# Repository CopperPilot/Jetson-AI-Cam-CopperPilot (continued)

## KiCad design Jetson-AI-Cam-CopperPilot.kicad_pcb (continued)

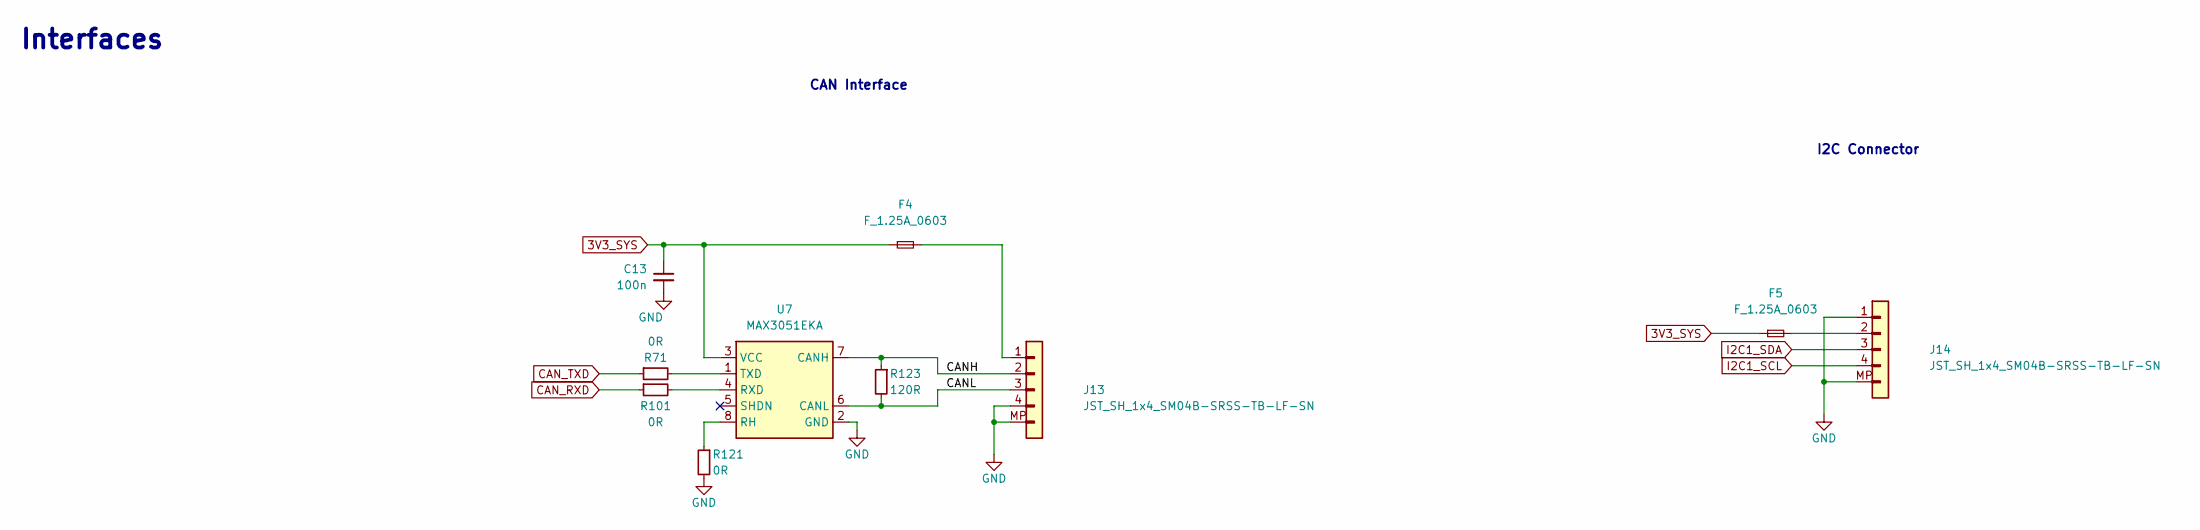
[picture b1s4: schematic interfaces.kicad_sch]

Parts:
C13: C_100n_0402; C_0402_1005Metric; Voltage 50V; MPN GRM155R61H104KE14D; LCSC C1525
F4, F5: F_1.25A_0603; F_0603_1608Metric; MPN 04671.25NR; LCSC C150891
J13, J14: JST_SH_1x4_SM04B-SRSS-TB-LF-SN; Conn_JST_SH_1x4_SM04B-SRSS-TB-LF-SN; MPN SM04B-SRSS-TB(LF)(SN); LCSC C160404
R71, R101, R121: R_0R_0402; R_0402_1005Metric; MPN ERJ2GE0R00X; LCSC C17168
R123: R_120R_0402; R_0402_1005Metric; Tolerance 1%; MPN CR0402-FX-1200GLF; LCSC C25079
U7: MAX3051EKA; SOT-23-8; MPN MAX3051EKA; LCSC C90741

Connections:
3V3_SYS: C13.1, F4.1, F5.1, U7.3 (VCC); also elsewhere on the board
/Interfaces/CANH: J13.2, R123.1, U7.7 (CANH)
/Interfaces/CANL: J13.3, R123.2, U7.6 (CANL)
CAN_RXD: R101.1; also elsewhere on the board
CAN_TXD: R71.1; also elsewhere on the board
GND: C13.2, J13.4, J13.MP, J14.1, J14.MP, R121.2, U7.2 (GND); also elsewhere on the board
I2C1_SCL: J14.4; also elsewhere on the board
I2C1_SDA: J14.3; also elsewhere on the board
unnamed: F4.2, J13.1
unnamed: F5.2, J14.2
unnamed: R121.1, U7.8 (RH)
unnamed: R101.2, U7.4 (RXD)
unnamed: R71.2, U7.1 (TXD)

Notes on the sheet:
I2C Connector
CAN Interface
Interfaces

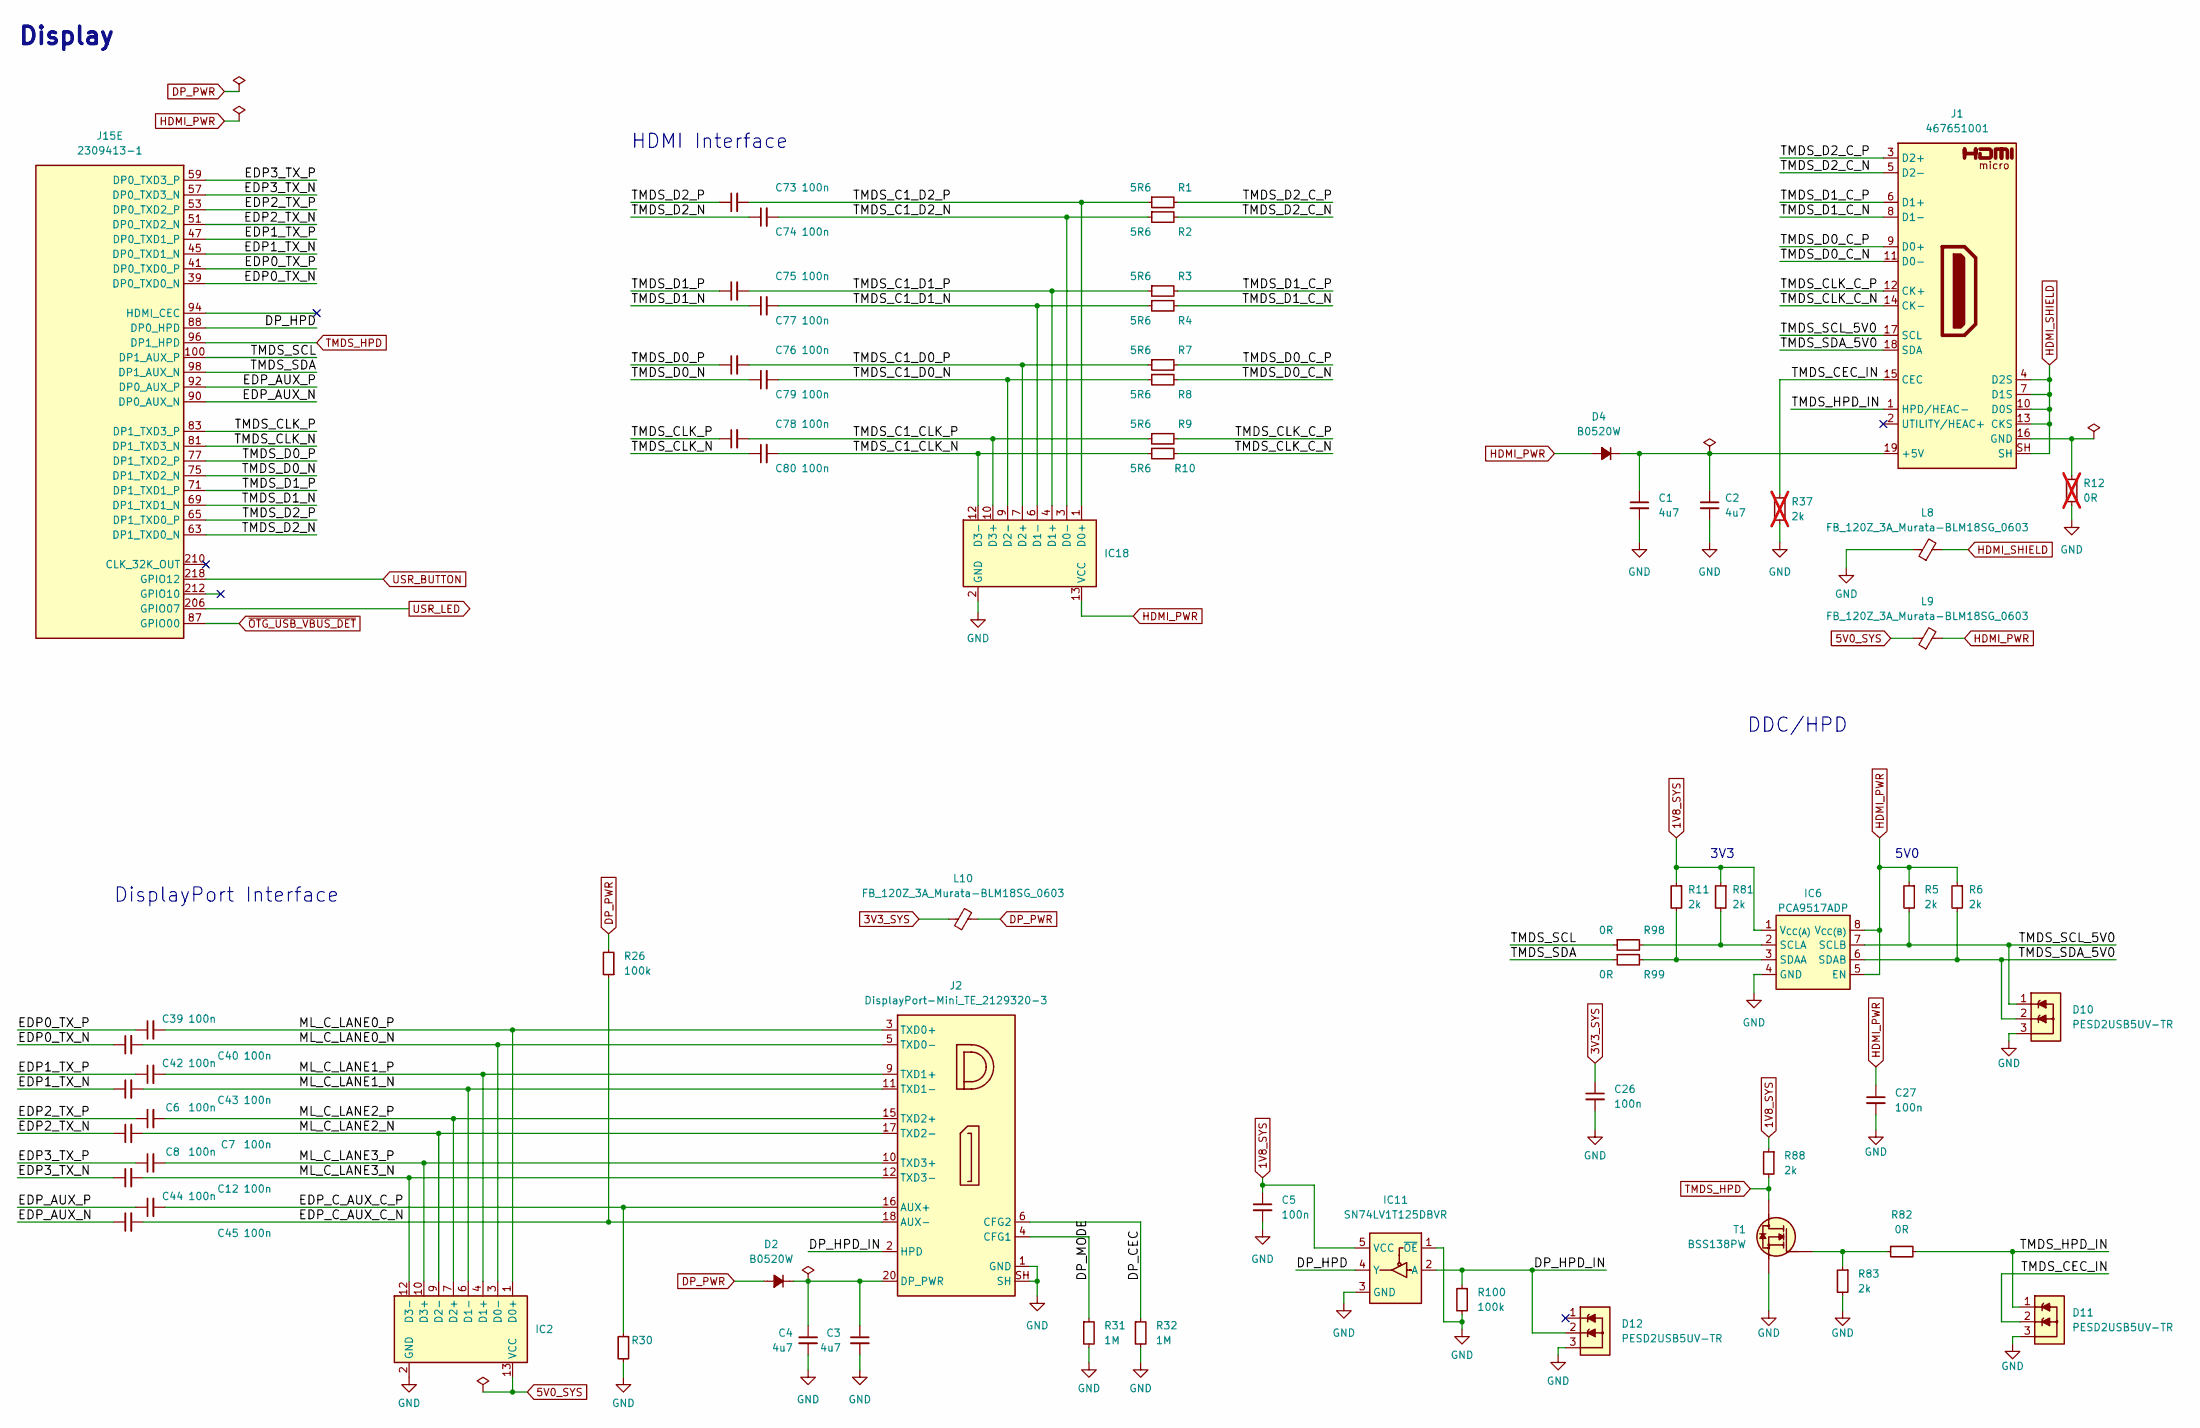
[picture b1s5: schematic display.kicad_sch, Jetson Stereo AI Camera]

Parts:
C1, C2, C3, C4: C_4u7_0402; C_0402_1005Metric; MPN GRM155R61A475MEAAD; LCSC C23733
C5, C6, C7, C8, C12, C26, C27, C39, C40, C42, C43, C44, C45, C73, C74, C75, C76, C77, C78, C79, C80: C_100n_0402; C_0402_1005Metric; Voltage 50V; MPN GRM155R61H104KE14D; LCSC C1525
D2, D4: B0520W; D_SOD-323F; MPN B0520W; LCSC C8598
D10, D11, D12: PESD2USB5UV-TR; SOT-23-3; MPN PESD2USB5UV-TR; LCSC C2827695
IC2, IC18: TPD8S009DSMR; R-PDSO-N15; PartSymbol TPD8S009DSMR; LCSC C139543
IC6: PCA9517ADP; TSSOP-8_3x3mm_P0.65mm; MPN PCA9517ADP; LCSC C112457
IC11: SN74LV1T125DBVR; SOT-23-5; MPN SN74LV1T125DBVR; LCSC C100024
J1: HDMI-Micro-D_Molex_467561001; HDMI-Micro-D_Receptacle_Molex_467651001; MPN 467651001; LCSC C563878
J2: DisplayPort-Mini_TE_2129320-3; DisplayPort-Mini_Receptacle_TE_2129320-3; MPN 2129320-3; LCSC C574827
J15: Bus_DDR4_SODIMM_CUSTOM_Jetson-Nano-H9.2mm-socket; TE_2309413; PartSymbol 2309413-1; LCSC C2766246
L8, L9, L10: FB_120Z_3A_Murata-BLM18SG_0603; FB_0603_1608Metric; MPN BLM18SG121TN1D; LCSC C73884
R1, R2, R3, R4, R7, R8, R9, R10: R_5R6_0402; R_0402_1005Metric; Tolerance 1%; MPN CR0402-FX-5R60GLF; LCSC C25122
R5, R6, R11, R81, R83, R88: R_2k_0402; R_0402_1005Metric; Tolerance 1%; MPN CR0402-FX-2001GLF; LCSC C4109
R12: R_0R_0402; R_0402_1005Metric; MPN ERJ2GE0R00X; LCSC C17168; not fitted
R26, R30, R100: R_100k_0402; R_0402_1005Metric; Tolerance 1%; MPN CR0402-FX-1003GLF; LCSC C25741
R31, R32: R_1M_0402; R_0402_1005Metric; Tolerance 1%; MPN CR0402-FX-1004GLF; LCSC C26083
R37: R_2k_0402; R_0402_1005Metric; Tolerance 1%; MPN CR0402-FX-2001GLF; LCSC C4109; not fitted
R82, R98, R99: R_0R_0402; R_0402_1005Metric; MPN ERJ2GE0R00X; LCSC C17168
T1: BSS138PW; SC70-3; MPN BSS138PW; LCSC C84617

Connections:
1V8_SYS: C5.1, IC6.1 (V_{CC(A)}), IC11.5 (VCC), R11.1, R81.1, R88.1; also elsewhere on the board
3V3_SYS: C26.1, L10.1; also elsewhere on the board
5V0_SYS: IC2.13 (VCC), IC2.15 (VCC), L9.1; also elsewhere on the board
/Display/DP_CEC: J2.6 (CFG2), R32.1
/Display/DP_HPD: IC11.4 (Y), J15.88 (DP0_HPD)
/Display/DP_HPD_IN: D12.2, IC11.2 (A), J2.2 (HPD), R100.1
/Display/DP_MODE: J2.4 (CFG1), R31.1
/Display/EDP0_TX_N: C40.1, J15.39 (DP0_TXD0_N)
/Display/EDP0_TX_P: C39.1, J15.41 (DP0_TXD0_P)
/Display/EDP1_TX_N: C43.1, J15.45 (DP0_TXD1_N)
/Display/EDP1_TX_P: C42.1, J15.47 (DP0_TXD1_P)
/Display/EDP2_TX_N: C7.1, J15.51 (DP0_TXD2_N)
/Display/EDP2_TX_P: C6.1, J15.53 (DP0_TXD2_P)
/Display/EDP3_TX_N: C12.1, J15.57 (DP0_TXD3_N)
/Display/EDP3_TX_P: C8.1, J15.59 (DP0_TXD3_P)
/Display/EDP_AUX_N: C45.1, J15.90 (DP0_AUX_N)
/Display/EDP_AUX_P: C44.1, J15.92 (DP0_AUX_P)
/Display/EDP_C_AUX_C_N: C45.2, J2.18 (AUX-), R26.1
/Display/EDP_C_AUX_C_P: C44.2, J2.16 (AUX+), R30.1
/Display/ML_C_LANE0_N: C40.2, IC2.3 (D0-), J2.5 (TXD0-)
/Display/ML_C_LANE0_P: C39.2, IC2.1 (D0+), J2.3 (TXD0+)
/Display/ML_C_LANE1_N: C43.2, IC2.6 (D1-), J2.11 (TXD1-)
/Display/ML_C_LANE1_P: C42.2, IC2.4 (D1+), J2.9 (TXD1+)
/Display/ML_C_LANE2_N: C7.2, IC2.9 (D2-), J2.17 (TXD2-)
/Display/ML_C_LANE2_P: C6.2, IC2.7 (D2+), J2.15 (TXD2+)
/Display/ML_C_LANE3_N: C12.2, IC2.12 (D3-), J2.12 (TXD3-)
/Display/ML_C_LANE3_P: C8.2, IC2.10 (D3+), J2.10 (TXD3+)
/Display/TMDS_C1_CLK_N: C80.2, IC18.12 (D3-), R10.1
/Display/TMDS_C1_CLK_P: C78.2, IC18.10 (D3+), R9.1
/Display/TMDS_C1_D0_N: C79.2, IC18.9 (D2-), R8.1
/Display/TMDS_C1_D0_P: C76.2, IC18.7 (D2+), R7.1
/Display/TMDS_C1_D1_N: C77.2, IC18.6 (D1-), R4.1
/Display/TMDS_C1_D1_P: C75.2, IC18.4 (D1+), R3.1
/Display/TMDS_C1_D2_N: C74.2, IC18.3 (D0-), R2.1
/Display/TMDS_C1_D2_P: C73.2, IC18.1 (D0+), R1.1
/Display/TMDS_CEC_IN: D11.2, J1.15 (CEC), R37.1
/Display/TMDS_CLK_C_N: J1.14 (CK-), R10.2
/Display/TMDS_CLK_C_P: J1.12 (CK+), R9.2
/Display/TMDS_CLK_N: C80.1, J15.81 (DP1_TXD3_N)
/Display/TMDS_CLK_P: C78.1, J15.83 (DP1_TXD3_P)
/Display/TMDS_D0_C_N: J1.11 (D0-), R8.2
/Display/TMDS_D0_C_P: J1.9 (D0+), R7.2
/Display/TMDS_D0_N: C79.1, J15.75 (DP1_TXD2_N)
/Display/TMDS_D0_P: C76.1, J15.77 (DP1_TXD2_P)
/Display/TMDS_D1_C_N: J1.8 (D1-), R4.2
/Display/TMDS_D1_C_P: J1.6 (D1+), R3.2
/Display/TMDS_D1_N: C77.1, J15.69 (DP1_TXD1_N)
/Display/TMDS_D1_P: C75.1, J15.71 (DP1_TXD1_P)
/Display/TMDS_D2_C_N: J1.5 (D2-), R2.2
/Display/TMDS_D2_C_P: J1.3 (D2+), R1.2
/Display/TMDS_D2_N: C74.1, J15.63 (DP1_TXD0_N)
/Display/TMDS_D2_P: C73.1, J15.65 (DP1_TXD0_P)
/Display/TMDS_HPD_IN: D11.1, J1.1 (HPD/HEAC-), R82.2
/Display/TMDS_SCL: J15.100 (DP1_AUX_P), R98.1
/Display/TMDS_SCL_5V0: D10.1, IC6.7 (SCLB), J1.17 (SCL), R5.2
/Display/TMDS_SDA: J15.98 (DP1_AUX_N), R99.1
/Display/TMDS_SDA_5V0: D10.2, IC6.6 (SDAB), J1.18 (SDA), R6.2
DP_PWR: D2.2 (A), L10.2, R26.2
GND: C1.2, C2.2, C3.2, C4.2, C5.2, C26.2, C27.2, D10.3, D11.3, D12.3, IC2.2 (GND), IC2.5 (GND), IC2.8 (GND), IC2.11 (GND), IC6.4 (GND), IC11.1 (~OE), IC11.3 (GND), IC18.2 (GND), IC18.5 (GND), IC18.8 (GND), IC18.11 (GND), J2.1 (GND), J2.7 (GND), J2.8 (GND), J2.13 (GND), J2.14 (GND), J2.19 (GND), J2.SH, L8.1, R12.2, R30.2, R31.2, R32.2, R37.2, R83.2, R100.2, T1.2 (S); also elsewhere on the board
HDMI_PWR: C27.1, D4.2 (A), IC6.5 (EN), IC6.8 (V_{CC(B)}), IC18.13 (VCC), IC18.15 (VCC), L9.2, R5.1, R6.1
HDMI_SHIELD: J1.4 (D2S), J1.7 (D1S), J1.10 (D0S), J1.13 (CKS), J1.SH, L8.2
unnamed: C3.1, C4.1, D2.1 (C), J2.20 (DP_PWR)
unnamed: C1.1, C2.1, D4.1 (C), J1.19 (+5V)
unnamed: IC6.2 (SCLA), R81.2, R98.2
unnamed: IC6.3 (SDAA), R11.2, R99.2
unnamed: J1.16 (GND), R12.1
unnamed: R82.1, R83.1, T1.1 (G)
TMDS_HPD: J15.96 (DP1_HPD), R88.2, T1.3 (D)
USR_BUTTON: J15.218 (GPIO12); also elsewhere on the board
USR_LED: J15.206 (GPIO07); also elsewhere on the board
~OTG_USB_VBUS_DET: J15.87 (GPIO00); also elsewhere on the board

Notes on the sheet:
5V0
DDC/HPD
3V3
HDMI Interface
DisplayPort Interface
Display

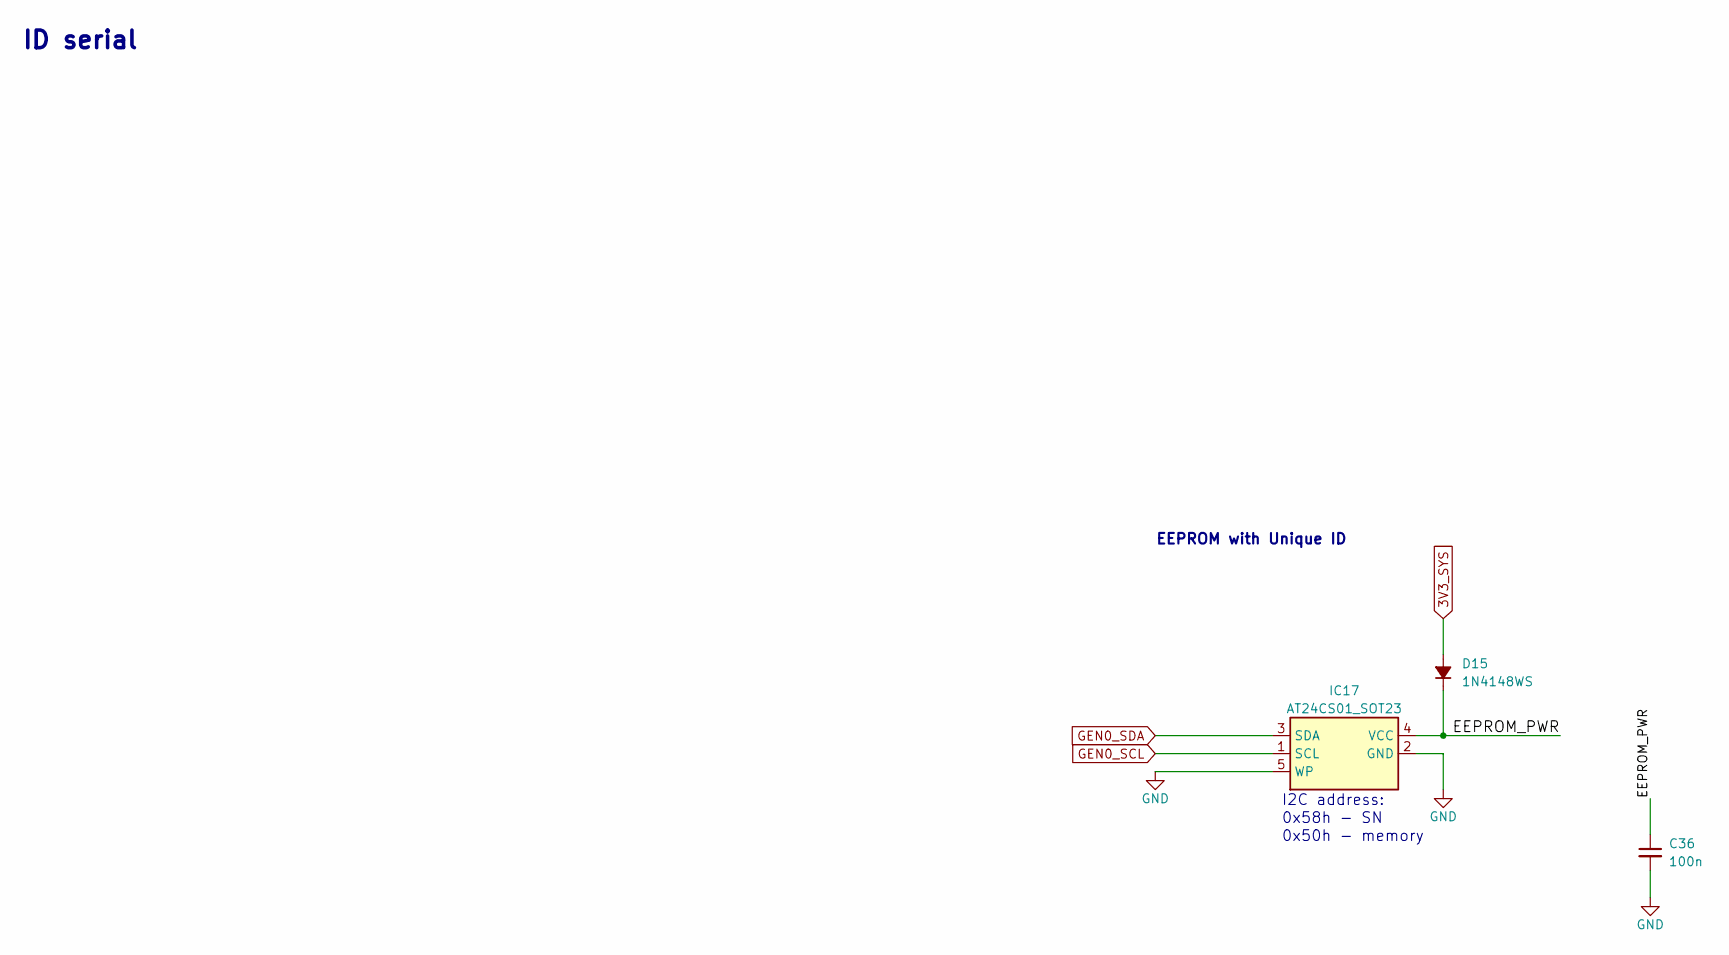
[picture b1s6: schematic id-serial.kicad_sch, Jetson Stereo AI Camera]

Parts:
C36: C_100n_0402; C_0402_1005Metric; Voltage 50V; MPN GRM155R61H104KE14D; LCSC C1525
D15: 1N4148WS; D_SOD-323F; MPN 1N4148WS; LCSC C2128
IC17: AT24CS01_SOT23; SOT-23-5; MPN AT24CS01-ST; LCSC C500682

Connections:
3V3_SYS: D15.2 (A); also elsewhere on the board
/ID Serial/EEPROM_PWR: C36.1, D15.1 (C), IC17.4 (VCC)
GEN0_SCL: IC17.1 (SCL); also elsewhere on the board
GEN0_SDA: IC17.3 (SDA); also elsewhere on the board
GND: C36.2, IC17.2 (GND), IC17.5 (WP); also elsewhere on the board

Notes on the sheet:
ID serial
0x50h - memory
I2C address:
0x58h - SN
EEPROM with Unique ID

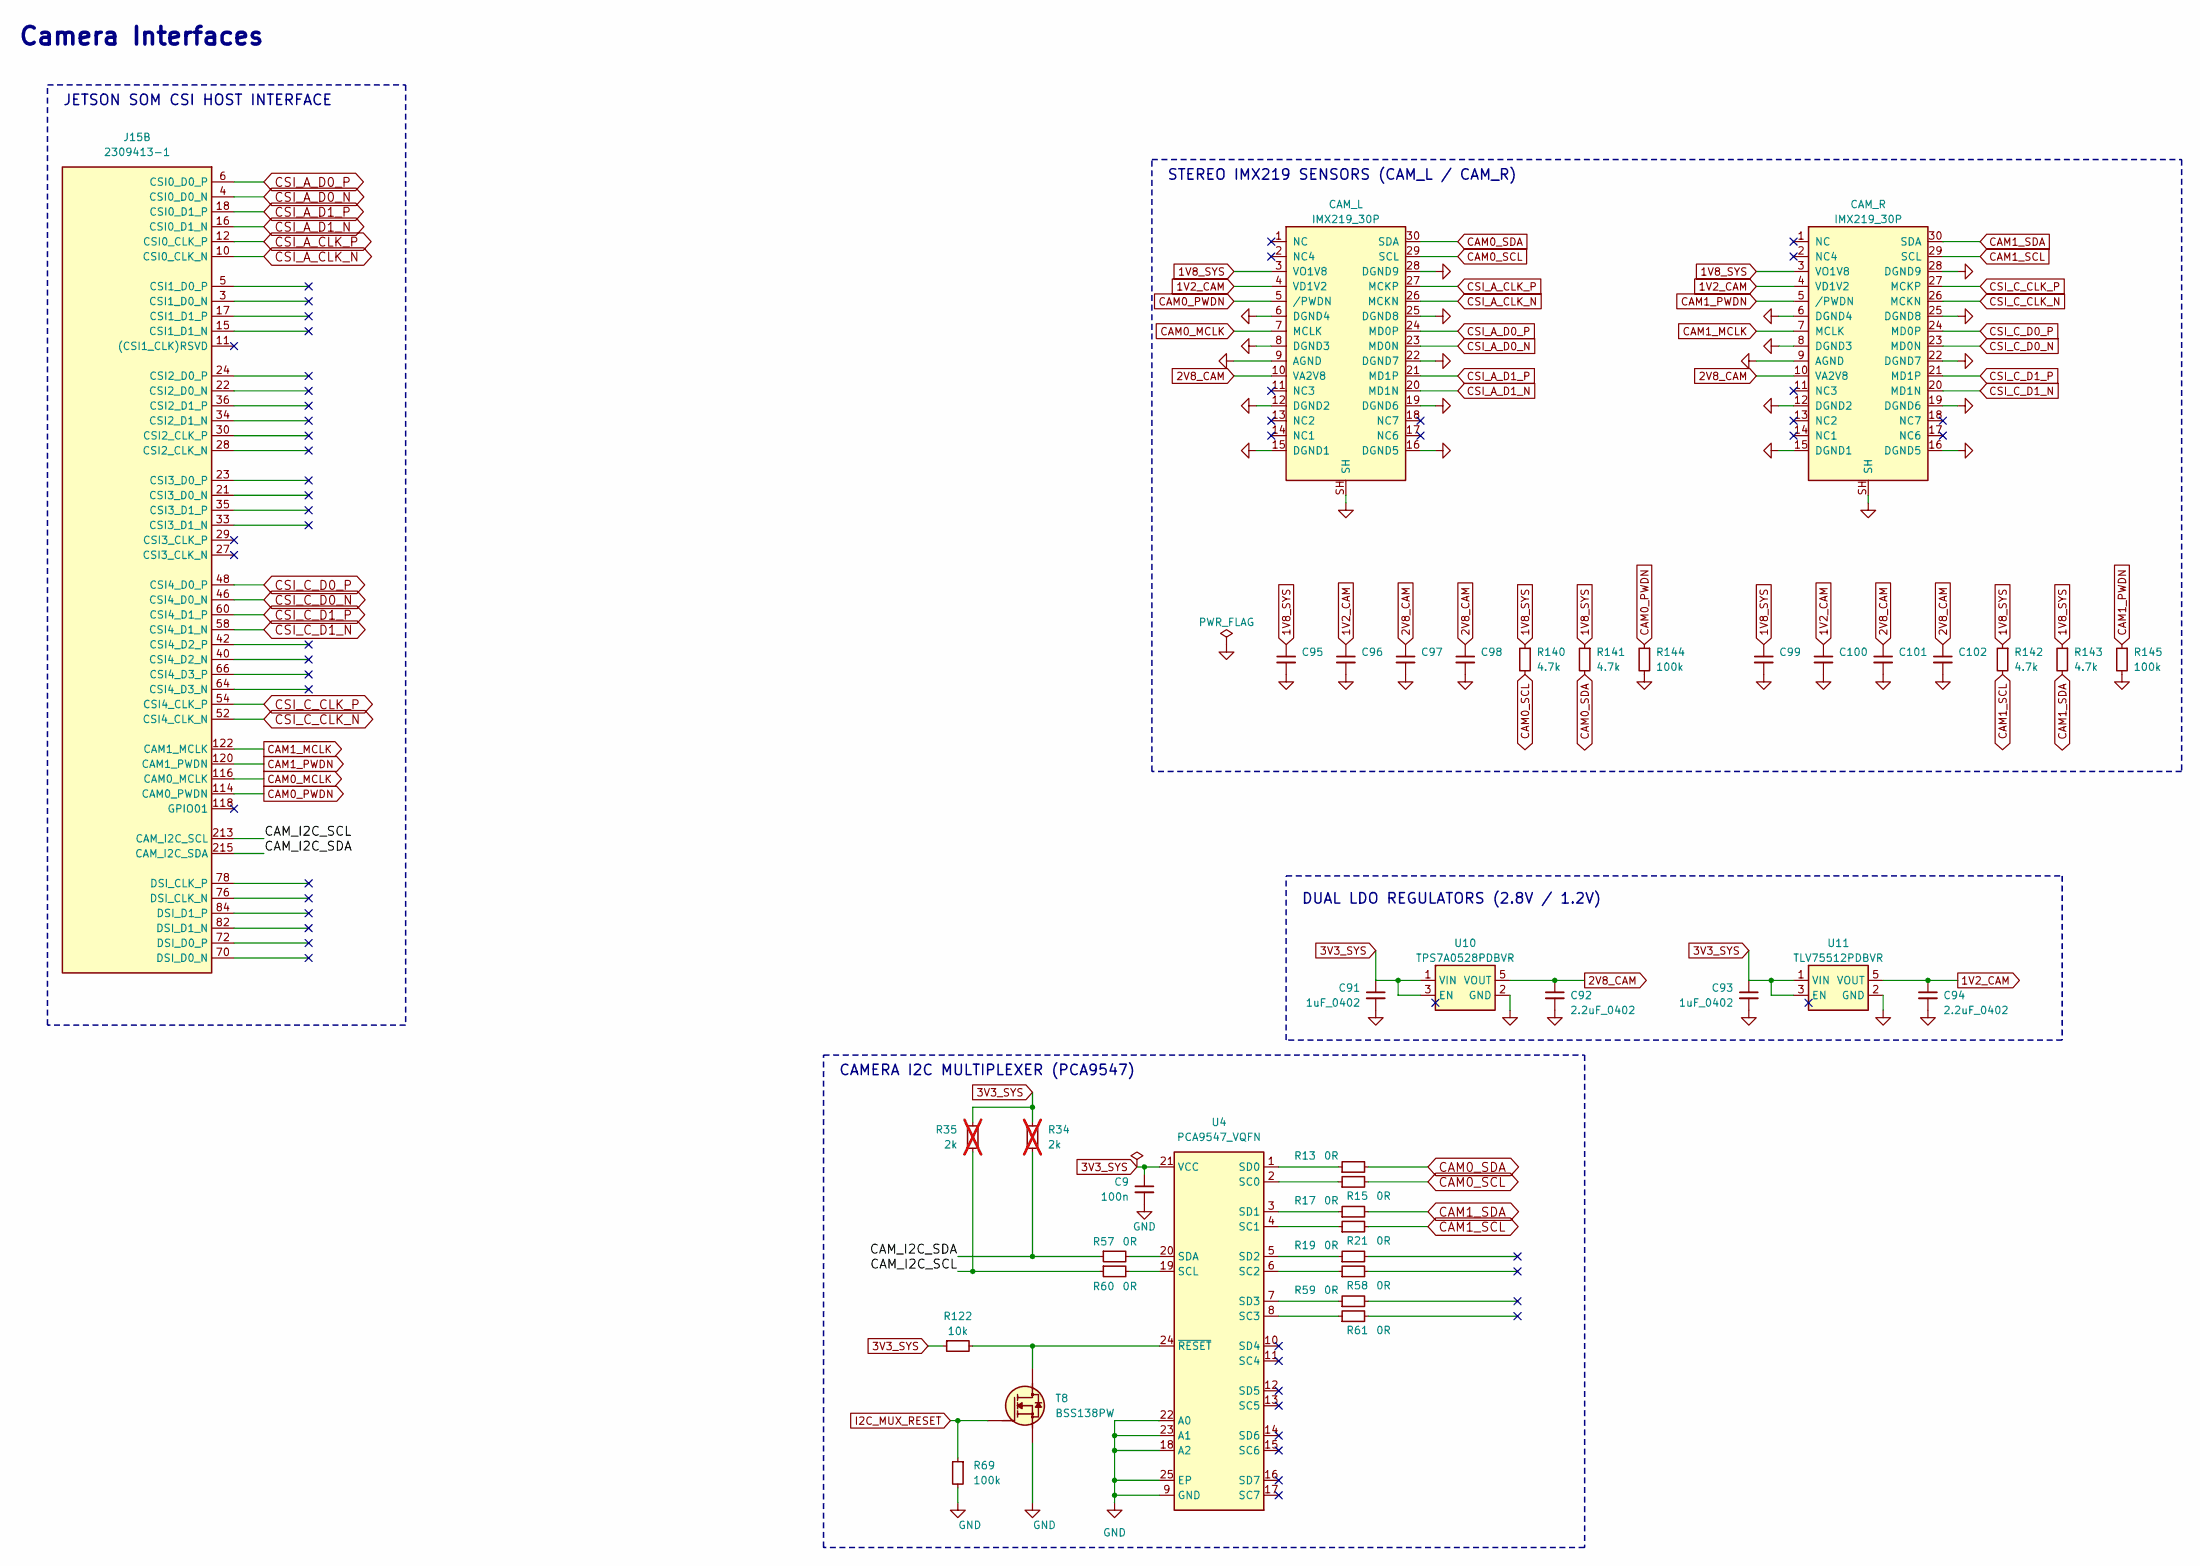
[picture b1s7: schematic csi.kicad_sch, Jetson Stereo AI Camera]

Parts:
C9: C_100n_0402; C_0402_1005Metric; Voltage 50V; MPN GRM155R61H104KE14D; LCSC C1525
C91, C93: 1uF_0402; C_0402_1005Metric; MPN C1005X6S1A105K050BC; LCSC C52923
C92, C94: 2.2uF_0402; C_0402_1005Metric; MPN C1005X5R1A225K050BC; LCSC C12530
C95, C96, C97, C99, C100, C101: C_100n_0402; C_0402_1005Metric; MPN GRM155R61H104KE14D; LCSC C1525
C98, C102: C_2u2_0402; C_0402_1005Metric; MPN C1005X5R1A225K050BC; LCSC C12530
CAM_L: IMX219_30P; Camera_Module_IMX219-D160; MPN BM20B(0.8)-30DS-0.4V(51); LCSC C424662
CAM_R: IMX219_30P; Camera_Module_IMX219-D160; MPN BM20B(0.8)-30DS-0.4V(51); LCSC C424662
J15: Bus_DDR4_SODIMM_CUSTOM_Jetson-Nano-H9.2mm-socket; TE_2309413; PartSymbol 2309413-1; LCSC C2766246
R13, R15, R17, R19, R21, R57, R58, R59, R60, R61: R_0R_0402; R_0402_1005Metric; MPN ERJ2GE0R00X; LCSC C17168
R34, R35: R_2k_0402; R_0402_1005Metric; Tolerance 1%; MPN CR0402-FX-2001GLF; LCSC C4109; not fitted
R69: R_100k_0402; R_0402_1005Metric; Tolerance 1%; MPN CR0402-FX-1003GLF; LCSC C25741
R122: R_10k_0402; R_0402_1005Metric; Tolerance 1%; MPN CR0402-FX-1002GLF; LCSC C25744
R140, R141, R142, R143: 4.7k; R_0402_1005Metric; MPN CR0402-FX-4701GLF; LCSC C25900
R144, R145: 100k; R_0402_1005Metric; MPN CR0402-FX-1003GLF; LCSC C25741
T8: BSS138PW; SC70-3; MPN BSS138PW; LCSC C84617
U4: PCA9547_VQFN; VQFN-24-1EP_3.8x3.8x1.0mm_P0.5mm; MPN PCA9547BS,118; LCSC C138804
U10: TPS7A0528PDBVR; SOT-23-5; MPN TPS7A0528PDBVR; LCSC C194387
U11: TLV75512PDBVR; SOT-23-5; MPN TLV75512PDBVR; LCSC C485675

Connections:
1V2_CAM: C94.1, C96.1, C100.1, CAM_L.4 (VD1V2), CAM_R.4 (VD1V2), U11.5 (VOUT)
1V8_SYS: C95.1, C99.1, CAM_L.3 (VO1V8), CAM_R.3 (VO1V8), R140.1, R141.1, R142.1, R143.1; also elsewhere on the board
2V8_CAM: C92.1, C97.1, C98.1, C101.1, C102.1, CAM_L.10 (VA2V8), CAM_R.10 (VA2V8), U10.5 (VOUT)
3V3_SYS: C9.1, C91.1, C93.1, R34.1, R35.1, R122.1, U4.21 (VCC), U10.1 (VIN), U10.3 (EN), U11.1 (VIN), U11.3 (EN); also elsewhere on the board
/CSI/CAM_I2C_SCL: J15.213 (CAM_I2C_SCL), R35.2, R60.1
/CSI/CAM_I2C_SDA: J15.215 (CAM_I2C_SDA), R34.2, R57.1
CAM0_MCLK: CAM_L.7 (MCLK), J15.116 (CAM0_MCLK)
CAM0_PWDN: CAM_L.5 (/PWDN), J15.114 (CAM0_PWDN), R144.1
CAM0_SCL: CAM_L.29 (SCL), R15.2, R140.2
CAM0_SDA: CAM_L.30 (SDA), R13.2, R141.2
CAM1_MCLK: CAM_R.7 (MCLK), J15.122 (CAM1_MCLK)
CAM1_PWDN: CAM_R.5 (/PWDN), J15.120 (CAM1_PWDN), R145.1
CAM1_SCL: CAM_R.29 (SCL), R21.2, R142.2
CAM1_SDA: CAM_R.30 (SDA), R17.2, R143.2
CSI_A_CLK_N: CAM_L.26 (MCKN), J15.10 (CSI0_CLK_N)
CSI_A_CLK_P: CAM_L.27 (MCKP), J15.12 (CSI0_CLK_P)
CSI_A_D0_N: CAM_L.23 (MD0N), J15.4 (CSI0_D0_N)
CSI_A_D0_P: CAM_L.24 (MD0P), J15.6 (CSI0_D0_P)
CSI_A_D1_N: CAM_L.20 (MD1N), J15.16 (CSI0_D1_N)
CSI_A_D1_P: CAM_L.21 (MD1P), J15.18 (CSI0_D1_P)
CSI_C_CLK_N: CAM_R.26 (MCKN), J15.52 (CSI4_CLK_N)
CSI_C_CLK_P: CAM_R.27 (MCKP), J15.54 (CSI4_CLK_P)
CSI_C_D0_N: CAM_R.23 (MD0N), J15.46 (CSI4_D0_N)
CSI_C_D0_P: CAM_R.24 (MD0P), J15.48 (CSI4_D0_P)
CSI_C_D1_N: CAM_R.20 (MD1N), J15.58 (CSI4_D1_N)
CSI_C_D1_P: CAM_R.21 (MD1P), J15.60 (CSI4_D1_P)
GND: C9.2, C91.2, C92.2, C93.2, C94.2, C95.2, C96.2, C97.2, C98.2, C99.2, C100.2, C101.2, C102.2, CAM_L.6 (DGND4), CAM_L.8 (DGND3), CAM_L.9 (AGND), CAM_L.12 (DGND2), CAM_L.15 (DGND1), CAM_L.16 (DGND5), CAM_L.19 (DGND6), CAM_L.22 (DGND7), CAM_L.25 (DGND8), CAM_L.28 (DGND9), CAM_L.SH, CAM_R.6 (DGND4), CAM_R.8 (DGND3), CAM_R.9 (AGND), CAM_R.12 (DGND2), CAM_R.15 (DGND1), CAM_R.16 (DGND5), CAM_R.19 (DGND6), CAM_R.22 (DGND7), CAM_R.25 (DGND8), CAM_R.28 (DGND9), CAM_R.SH, R69.2, R144.2, R145.2, T8.2 (S), U4.9 (GND), U4.18 (A2), U4.22 (A0), U4.23 (A1), U4.25 (EP), U10.2 (GND), U11.2 (GND); also elsewhere on the board
I2C_MUX_RESET: R69.1, T8.1 (G); also elsewhere on the board
unnamed: R122.2, T8.3 (D), U4.24 (~RESET)
unnamed: R15.1, U4.2 (SC0)
unnamed: R21.1, U4.4 (SC1)
unnamed: R58.1, U4.6 (SC2)
unnamed: R61.1, U4.8 (SC3)
unnamed: R60.2, U4.19 (SCL)
unnamed: R13.1, U4.1 (SD0)
unnamed: R17.1, U4.3 (SD1)
unnamed: R19.1, U4.5 (SD2)
unnamed: R59.1, U4.7 (SD3)
unnamed: R57.2, U4.20 (SDA)

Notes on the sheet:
Camera Interfaces
JETSON SOM CSI HOST INTERFACE
CAMERA I2C MULTIPLEXER (PCA9547)
DUAL LDO REGULATORS (2.8V / 1.2V)
STEREO IMX219 SENSORS (CAM_L / CAM_R)

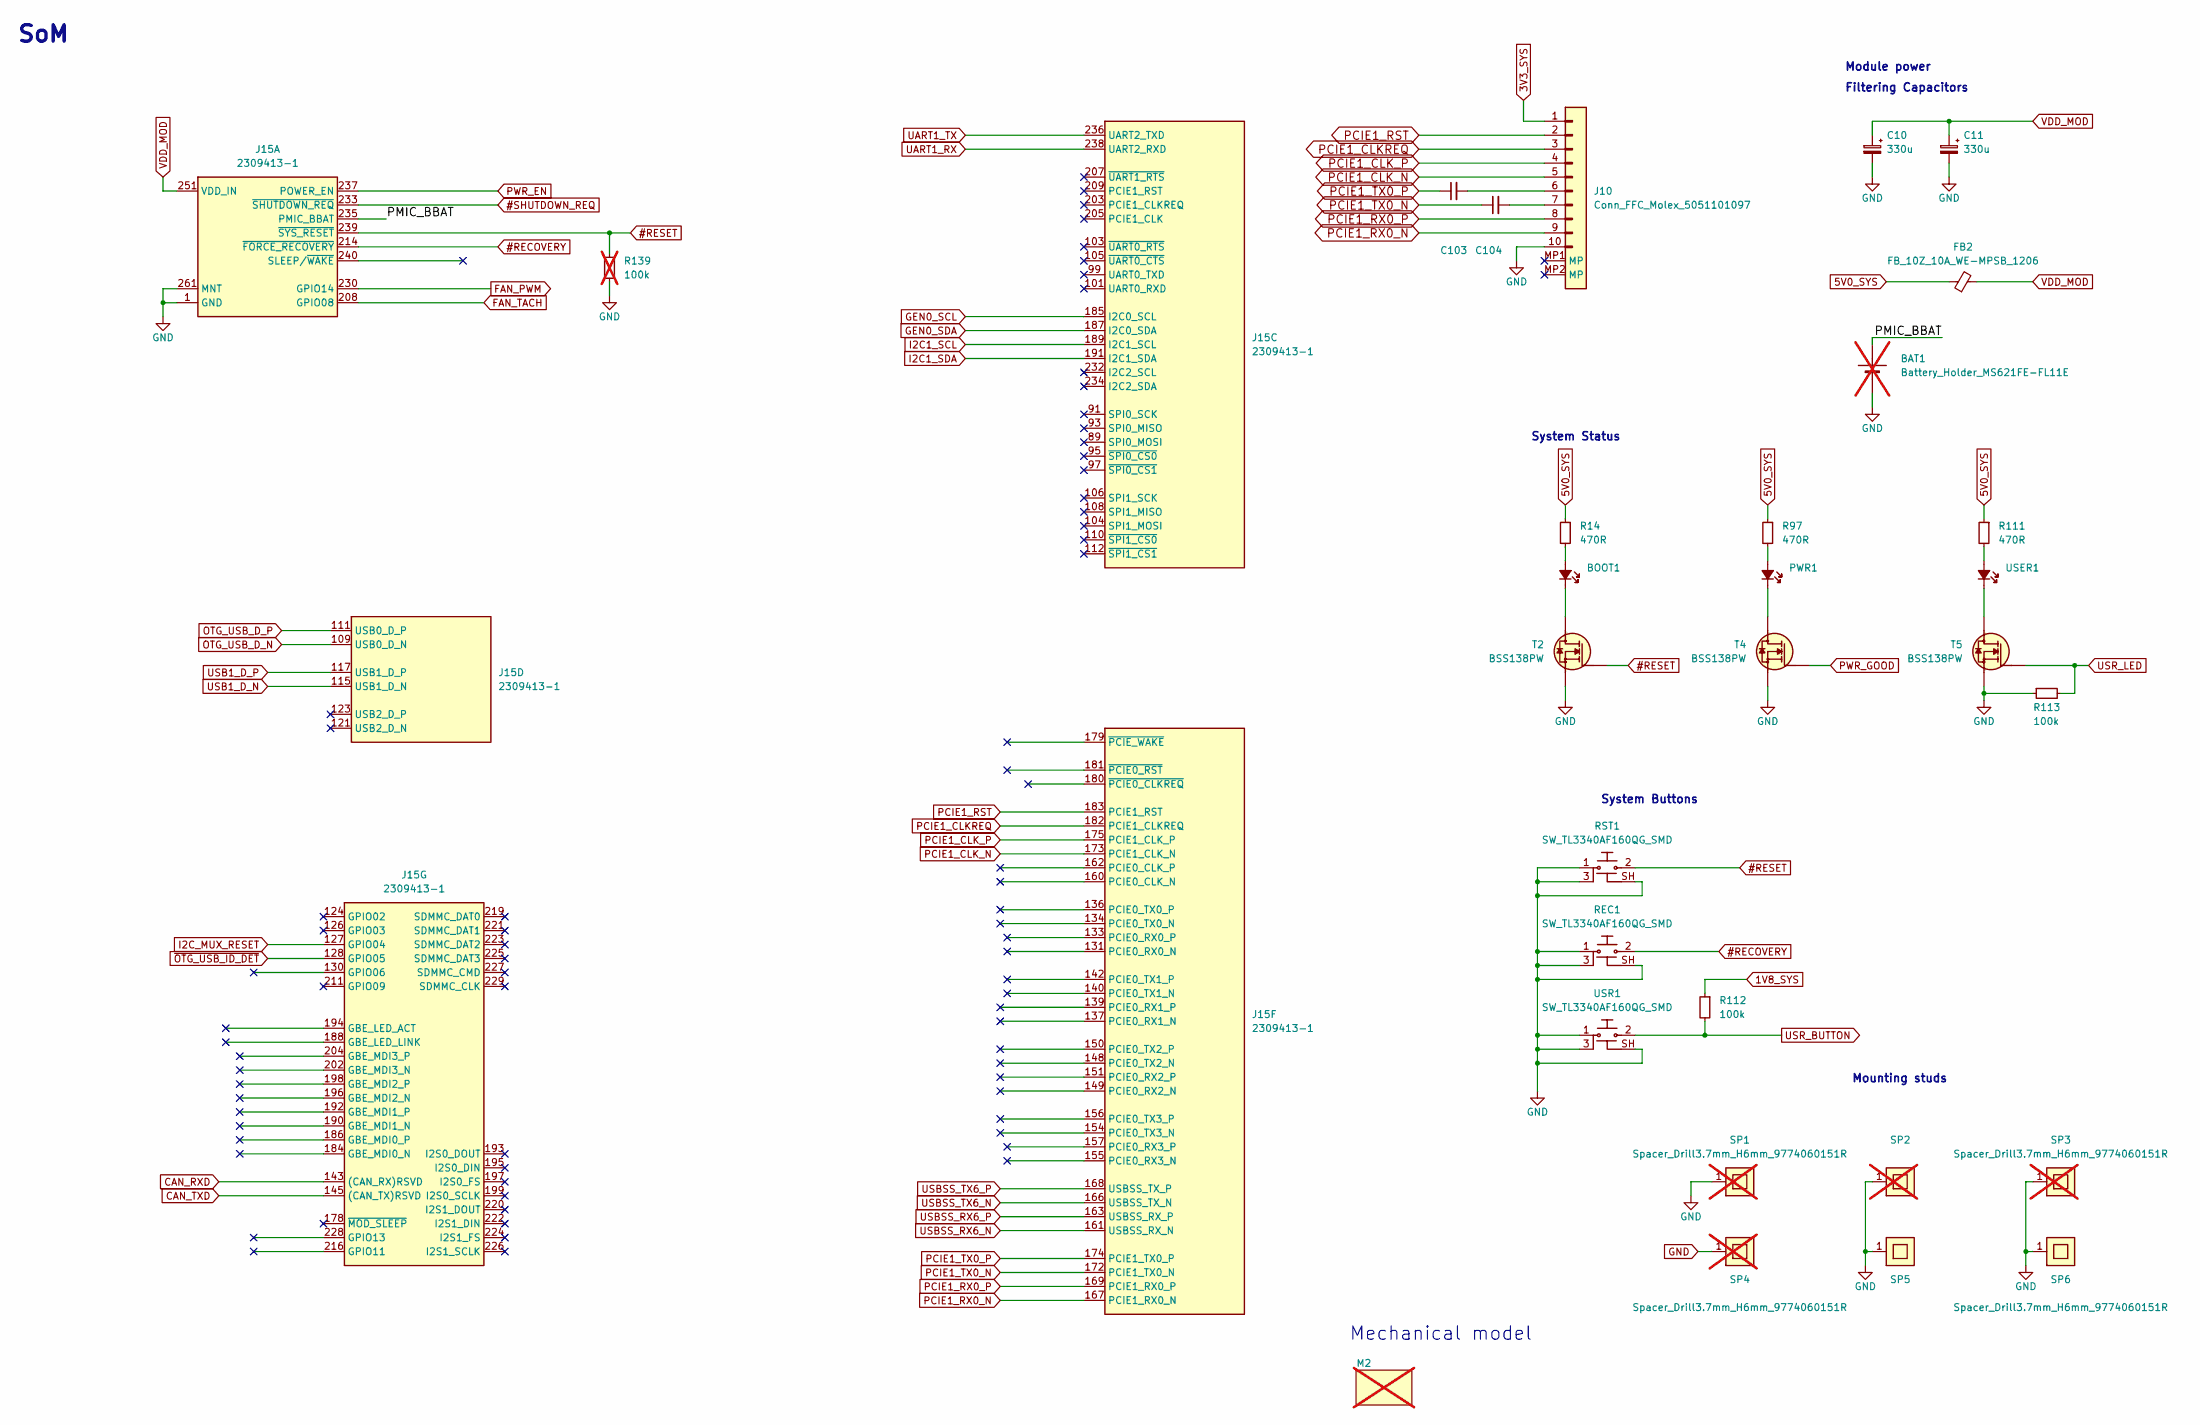
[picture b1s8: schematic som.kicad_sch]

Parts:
BAT1: Battery_Holder_MS621FE-FL11E; MS621FE-FL11E; MPN MS621FE-FL11E; LCSC C86703; not fitted
BOOT1: LED_G_0603_LG_L29K-G2J1-24-Z; LED_0603_1608Metric_G; MPN LG L29K-G2J1-24-Z; LCSC C72043
C10, C11: C_Pol_330u_6.3V_KEMET-T520-B; C_Pol_EIA-B; Voltage 6.3V; MPN T520B337M006ATE040; LCSC C134785
C103, C104: C_100n_0402; C_0402_1005Metric; MPN GRM155R61H104KE14D; LCSC C1525
FB2: FB_10Z_10A_WE-MPSB_1206; FB_1206_3216Metric; MPN 74279221100; LCSC C145764
J10: Conn_FFC_Molex_5051101097; MPN 5051101097; LCSC C283651
J15: Bus_DDR4_SODIMM_CUSTOM_Jetson-Nano-H9.2mm-socket; TE_2309413; PartSymbol 2309413-1; LCSC C2766246
M2: Jetson-Nano; Module_Jetson-Nano; MPN 945-13541-0000-0000; not fitted
PWR1: LED_G_0603_LG_L29K-G2J1-24-Z; LED_0603_1608Metric_G; MPN LG L29K-G2J1-24-Z; LCSC C72043
R14, R97, R111: R_470R_0402; R_0402_1005Metric; Tolerance 1%; MPN CR0402-FX-4700GLF; LCSC C25117
R112, R113: R_100k_0402; R_0402_1005Metric; Tolerance 1%; MPN CR0402-FX-1003GLF; LCSC C25741
R139: R_100k_0402; R_0402_1005Metric; Tolerance 1%; MPN CR0402-FX-1003GLF; LCSC C25741; not fitted
REC1: SW_TL3340AF160QG_SMD; MPN TL3340AF160QG; LCSC C2886925
RST1: SW_TL3340AF160QG_SMD; MPN TL3340AF160QG; LCSC C2886925
SP1, SP2, SP3, SP4: Spacer_Drill3.7mm_H6mm_9774060151R; MPN 9774060151R; LCSC C289551; not fitted
SP5, SP6: Spacer_Drill3.7mm_H6mm_9774060151R; MPN 9774060151R; LCSC C289551
T2, T4, T5: BSS138PW; SC70-3; MPN BSS138PW; LCSC C84617
USER1: LED_G_0603_LG_L29K-G2J1-24-Z; LED_0603_1608Metric_G; MPN LG L29K-G2J1-24-Z; LCSC C72043
USR1: SW_TL3340AF160QG_SMD; MPN TL3340AF160QG; LCSC C2886925

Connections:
1V8_SYS: R112.1; also elsewhere on the board
3V3_SYS: J10.1; also elsewhere on the board
5V0_SYS: FB2.1, R14.1, R97.1, R111.1; also elsewhere on the board
#RECOVERY: J15.214 (~FORCE_RECOVERY), REC1.2
#RESET: J15.239 (~SYS_RESET), R139.1, RST1.2, T2.1 (G); also elsewhere on the board
#SHUTDOWN_REQ: J15.233 (~SHUTDOWN_REQ); also elsewhere on the board
/SoM/PMIC_BBAT: BAT1.1 (+), J15.235 (PMIC_BBAT)
CAN_RXD: J15.143 ((CAN_RX)RSVD); also elsewhere on the board
CAN_TXD: J15.145 ((CAN_TX)RSVD); also elsewhere on the board
FAN_PWM: J15.230 (GPIO14); also elsewhere on the board
FAN_TACH: J15.208 (GPIO08); also elsewhere on the board
GEN0_SCL: J15.185 (I2C0_SCL); also elsewhere on the board
GEN0_SDA: J15.187 (I2C0_SDA); also elsewhere on the board
GND: BAT1.2 (-), C10.2, C11.2, J10.10, J15.1 (GND), J15.2 (GND), J15.7 (GND), J15.8 (GND), J15.13 (GND), J15.14 (GND), J15.19 (GND), J15.20 (GND), J15.25 (GND), J15.26 (GND), J15.31 (GND), J15.32 (GND), J15.37 (GND), J15.38 (GND), J15.43 (GND), J15.44 (GND), J15.49 (GND), J15.50 (GND), J15.55 (GND), J15.56 (GND), J15.61 (GND), J15.62 (GND), J15.67 (GND), J15.68 (GND), J15.73 (GND), J15.74 (GND), J15.79 (GND), J15.80 (GND), J15.85 (GND), J15.86 (GND), J15.102 (GND), J15.107 (GND), J15.113 (GND), J15.119 (GND), J15.125 (GND), J15.129 (GND), J15.132 (GND), J15.135 (GND), J15.138 (GND), J15.141 (GND), J15.144 (GND), J15.146 (GND), J15.147 (GND), J15.152 (GND), J15.153 (GND), J15.158 (GND), J15.159 (GND), J15.164 (GND), J15.165 (GND), J15.170 (GND), J15.171 (GND), J15.176 (GND), J15.177 (GND), J15.200 (GND), J15.201 (GND), J15.217 (GND), J15.231 (GND), J15.241 (GND), J15.242 (GND), J15.243 (GND), J15.244 (GND), J15.245 (GND), J15.246 (GND), J15.247 (GND), J15.248 (GND), J15.249 (GND), J15.250 (GND), J15.261 (MNT), J15.262 (MNT), R113.1, R139.2, REC1.1, REC1.3, REC1.SH, RST1.1, RST1.3, RST1.SH, SP1.1, SP2.1, SP3.1, SP5.1, SP6.1, T2.2 (S), T4.2 (S), T5.2 (S), USR1.1, USR1.3, USR1.SH; also elsewhere on the board
I2C1_SCL: J15.189 (I2C1_SCL); also elsewhere on the board
I2C1_SDA: J15.191 (I2C1_SDA); also elsewhere on the board
I2C_MUX_RESET: J15.127 (GPIO04); also elsewhere on the board
unnamed: BOOT1.2 (A), R14.2
unnamed: BOOT1.1 (C), T2.3 (D)
unnamed: C103.2, J10.6
unnamed: C104.2, J10.7
unnamed: PWR1.2 (A), R97.2
unnamed: PWR1.1 (C), T4.3 (D)
unnamed: T5.3 (D), USER1.1 (C)
unnamed: R111.2, USER1.2 (A)
OTG_USB_D_N: J15.109 (USB0_D_N); also elsewhere on the board
OTG_USB_D_P: J15.111 (USB0_D_P); also elsewhere on the board
PCIE1_CLKREQ: J10.3, J15.182 (PCIE1_CLKREQ)
PCIE1_CLK_N: J10.5, J15.173 (PCIE1_CLK_N)
PCIE1_CLK_P: J10.4, J15.175 (PCIE1_CLK_P)
PCIE1_RST: J10.2, J15.183 (PCIE1_RST)
PCIE1_RX0_N: J10.9, J15.167 (PCIE1_RX0_N)
PCIE1_RX0_P: J10.8, J15.169 (PCIE1_RX0_P)
PCIE1_TX0_N: C104.1, J15.172 (PCIE1_TX0_N)
PCIE1_TX0_P: C103.1, J15.174 (PCIE1_TX0_P)
PWR_EN: J15.237 (POWER_EN); also elsewhere on the board
PWR_GOOD: T4.1 (G); also elsewhere on the board
UART1_RX: J15.238 (UART2_RXD); also elsewhere on the board
UART1_TX: J15.236 (UART2_TXD); also elsewhere on the board
USB1_D_N: J15.115 (USB1_D_N); also elsewhere on the board
USB1_D_P: J15.117 (USB1_D_P); also elsewhere on the board
USBSS_RX6_N: J15.161 (USBSS_RX_N); also elsewhere on the board
USBSS_RX6_P: J15.163 (USBSS_RX_P); also elsewhere on the board
USBSS_TX6_N: J15.166 (USBSS_TX_N); also elsewhere on the board
USBSS_TX6_P: J15.168 (USBSS_TX_P); also elsewhere on the board
USR_BUTTON: R112.2, USR1.2; also elsewhere on the board
USR_LED: R113.2, T5.1 (G); also elsewhere on the board
VDD_MOD: C10.1, C11.1, FB2.2, J15.251 (VDD_IN), J15.252 (VDD_IN), J15.253 (VDD_IN), J15.254 (VDD_IN), J15.255 (VDD_IN), J15.256 (VDD_IN), J15.257 (VDD_IN), J15.258 (VDD_IN), J15.259 (VDD_IN), J15.260 (VDD_IN)
~OTG_USB_ID_DET: J15.128 (GPIO05); also elsewhere on the board

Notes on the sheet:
Module power
Mechanical model
Filtering Capacitors
System Buttons
SoM
System Status
Mounting studs
